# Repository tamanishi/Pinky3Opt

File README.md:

# Pinky3Opt

## Firmware

<https://github.com/tamanishi/qmk_firmware/tree/pinky3opt>

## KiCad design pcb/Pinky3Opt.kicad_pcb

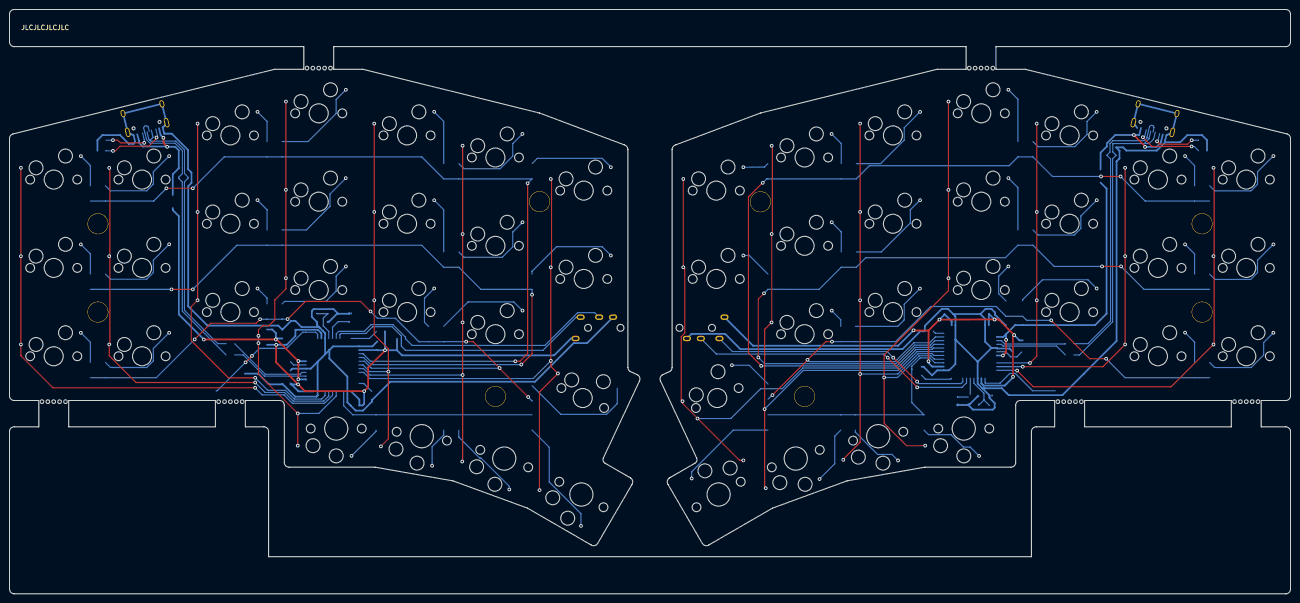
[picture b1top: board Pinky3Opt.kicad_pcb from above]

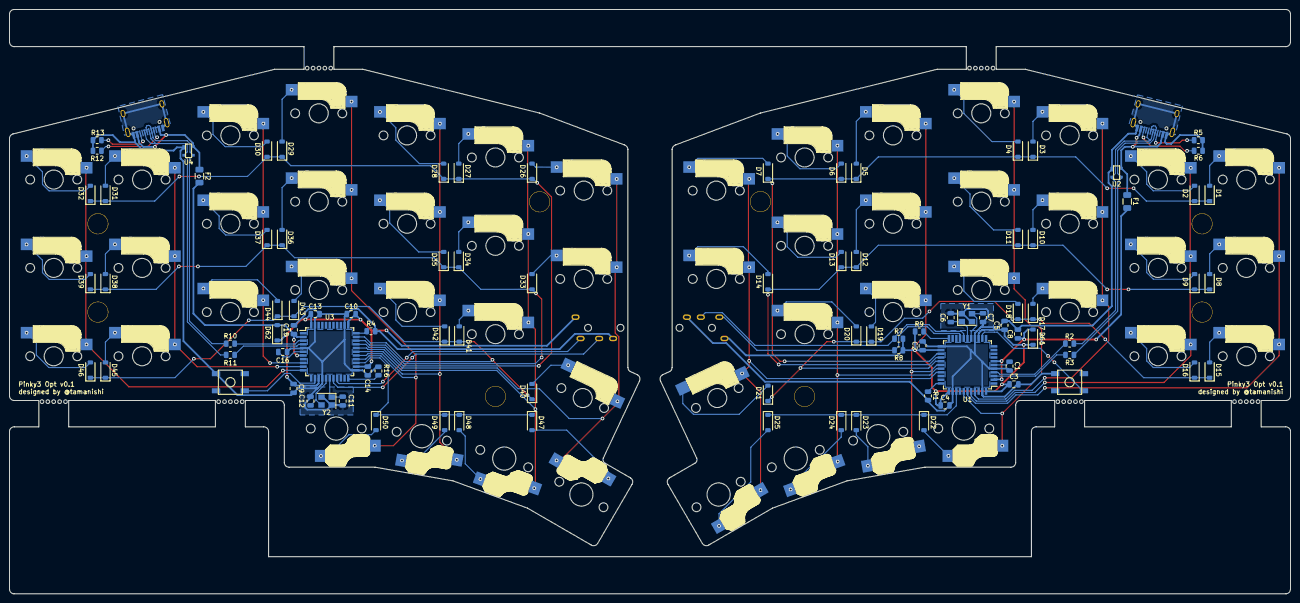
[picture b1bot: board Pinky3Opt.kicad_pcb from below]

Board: 2 copper layers, 276.2 x 126.0 mm, 154 parts (96 on the bottom side), 108 nets.

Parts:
C1, C16: 1uF; C_0805_2012Metric
C2, C3, C4, C5, C9, C10, C13, C14: 0.1uF; C_0805_2012Metric
C6, C7, C11, C12: 22pF; C_0805_2012Metric
C8, C15: 10uF; C_0805_2012Metric
D1, D2, D3, D4, D5, D6, D7, D8, D9, D10, D11, D12, D13, D14, D15, D16, D17, D18, D19, D20, D21, D22, D23, D24, D25, D26, D27, D28, D29, D30, D31, D32, D33, D34, D35, D36, D37, D38, D39, D40, D41, D42, D43, D44, D45, D46, D47, D48, D49, D50: D; D_SOD-123
D61, D62: D_Schottky; D_SOD-123
F1, F2: 500mA; Fuse_1206_3216Metric
J1, J3: USB_C_Receptacle_USB2.0; USB_C_Receptacle_HRO_TYPE-C-31-M-12
J2, J4: Conn_01x04; PJ-3200B-4A-Assembly
MX1, MX2, MX3, MX4, MX5, MX6, MX7, MX8, MX9, MX10, MX11, MX12, MX13, MX14, MX15, MX16, MX17, MX18, MX19, MX20, MX21, MX26, MX27, MX28, MX29, MX30, MX31, MX32, MX33, MX34, MX35, MX36, MX37, MX38, MX39, MX40, MX41, MX42, MX43, MX44, MX45, MX46: MX-NoLED; CherryMX_Hotswap
MX22, MX23, MX24, MX25, MX47, MX48, MX49, MX50: MX-NoLED; ChocV1_V2_Hotswap
R1, R4, R9, R16: 10kΩ; R_0805_2012Metric
R2, R3, R10, R11: 22Ω; R_0805_2012Metric
R5, R6, R12, R13: 5.1kΩ; R_0805_2012Metric
R7, R8: 4.7kΩ; R_0805_2012Metric
Ref**: Val**; m2_Spacer_Hole
Ref**#2, Ref**#3, Ref**#4, Ref**#5, Ref**#6, Ref**#7, Ref**#8: Val**; m2_Spacer_Hole
SW1, SW2: Reset; SKQGADE010
U1, U3: ATmega32U4-A; TQFP-44_10x10mm_P0.8mm
U2, U4: PRTR5V0U2X; SOT143B
Y1, Y2: 16MHz; Crystal_SMD_3225-4Pin_3.2x2.5mm

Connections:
+5V: C2.1, C3.1, C4.1, C5.1, D61.1 (K), J2.4, R7.1, R8.1, R9.2, U1.14 (VCC), U1.24 (AVCC), U1.34 (VCC), U1.44 (AVCC)
+5VA: C9.1, C10.1, C13.1, C14.1, D62.1 (K), J4.4, U3.14 (VCC), U3.24 (AVCC), U3.34 (VCC), U3.44 (AVCC)
/COL0_L: MX1.1 (COL), MX8.1 (COL), MX15.1 (COL), U1.39 (PF4)
/COL0_R: MX26.1 (COL), MX33.1 (COL), MX40.1 (COL), MX47.1 (COL), U3.29 (PB5)
/COL1_L: MX2.1 (COL), MX9.1 (COL), MX16.1 (COL), U1.40 (PF1)
/COL1_R: MX27.1 (COL), MX34.1 (COL), MX41.1 (COL), MX48.1 (COL), U3.28 (PB4)
/COL2_L: MX3.1 (COL), MX10.1 (COL), MX17.1 (COL), U1.41 (PF0)
/COL2_R: MX28.1 (COL), MX35.1 (COL), MX42.1 (COL), MX49.1 (COL), U3.27 (PD7)
/COL3_L: MX4.1 (COL), MX11.1 (COL), MX18.1 (COL), MX22.1 (COL), U1.38 (PF5)
/COL3_R: MX29.1 (COL), MX36.1 (COL), MX43.1 (COL), MX50.1 (COL), U3.26 (PD6)
/COL4_L: MX5.1 (COL), MX12.1 (COL), MX19.1 (COL), MX23.1 (COL), U1.28 (PB4)
/COL4_R: MX30.1 (COL), MX37.1 (COL), MX44.1 (COL), U3.9 (PB1)
/COL5_L: MX6.1 (COL), MX13.1 (COL), MX20.1 (COL), MX24.1 (COL), U1.29 (PB5)
/COL5_R: MX31.1 (COL), MX38.1 (COL), MX45.1 (COL), U3.10 (PB2)
/COL6_L: MX7.1 (COL), MX14.1 (COL), MX21.1 (COL), MX25.1 (COL), U1.30 (PB6)
/COL6_R: MX32.1 (COL), MX39.1 (COL), MX46.1 (COL), U3.11 (PB3)
/D+_L: R2.2, U1.4 (D+)
/D+_R: R11.2, U3.4 (D+)
/D-_L: R3.2, U1.3 (D-)
/D-_R: R10.2, U3.3 (D-)
/HDETECT_L: R9.1, U1.22 (PD5)
/HDETECT_R: R16.1, U3.22 (PD5)
/ROW0_L: D1.1 (K), D2.1 (K), D3.1 (K), D4.1 (K), D5.1 (K), D6.1 (K), D7.1 (K), U1.25 (PD4)
/ROW0_R: D26.1 (K), D27.1 (K), D28.1 (K), D29.1 (K), D30.1 (K), D31.1 (K), D32.1 (K), U3.30 (PB6)
/ROW1_L: D8.1 (K), D9.1 (K), D10.1 (K), D11.1 (K), D12.1 (K), D13.1 (K), D14.1 (K), U1.26 (PD6)
/ROW1_R: D33.1 (K), D34.1 (K), D35.1 (K), D36.1 (K), D37.1 (K), D38.1 (K), D39.1 (K), U3.31 (PC6)
/ROW2_L: D15.1 (K), D16.1 (K), D17.1 (K), D18.1 (K), D19.1 (K), D20.1 (K), D21.1 (K), U1.27 (PD7)
/ROW2_R: D40.1 (K), D41.1 (K), D42.1 (K), D43.1 (K), D44.1 (K), D45.1 (K), D46.1 (K), U3.32 (PC7)
/ROW3_L: D22.1 (K), D23.1 (K), D24.1 (K), D25.1 (K), U1.36 (PF7)
/ROW3_R: D47.1 (K), D48.1 (K), D49.1 (K), D50.1 (K), U3.25 (PD4)
/SCL_L: J2.2, R7.2, U1.18 (PD0)
/SCL_R: J4.2, U3.18 (PD0)
/SDA_L: J2.3, R8.2, U1.19 (PD1)
/SDA_R: J4.3, U3.19 (PD1)
GND: C1.2, C2.2, C3.2, C4.2, C5.2, C6.1, C7.1, C8.2, J1.A1 (GND), J1.A12 (GND), J1.B1 (GND), J1.B12 (GND), J1.S1 (SHIELD), J2.1, R1.2, R5.2, R6.2, SW1.1, U1.5 (UGND), U1.15 (GND), U1.23 (GND), U1.35 (GND), U1.43 (GND), U2.1 (GND), Y1.2, Y1.4
GNDA: C9.2, C10.2, C11.1, C12.1, C13.2, C14.2, C15.2, C16.2, J3.A1 (GND), J3.A12 (GND), J3.B1 (GND), J3.B12 (GND), J3.S1 (SHIELD), J4.1, R4.2, R12.2, R13.2, R16.2, SW2.1, U3.5 (UGND), U3.15 (GND), U3.23 (GND), U3.35 (GND), U3.43 (GND), U4.1 (GND), Y2.2, Y2.4
unnamed: D1.2 (A), MX1.2 (ROW)
unnamed: D2.2 (A), MX2.2 (ROW)
unnamed: D3.2 (A), MX3.2 (ROW)
unnamed: D4.2 (A), MX4.2 (ROW)
unnamed: D5.2 (A), MX5.2 (ROW)
unnamed: D6.2 (A), MX6.2 (ROW)
unnamed: D7.2 (A), MX7.2 (ROW)
unnamed: D8.2 (A), MX8.2 (ROW)
unnamed: D9.2 (A), MX9.2 (ROW)
unnamed: D10.2 (A), MX10.2 (ROW)
unnamed: D11.2 (A), MX11.2 (ROW)
unnamed: D12.2 (A), MX12.2 (ROW)
unnamed: D13.2 (A), MX13.2 (ROW)
unnamed: D14.2 (A), MX14.2 (ROW)
unnamed: D15.2 (A), MX15.2 (ROW)
unnamed: D16.2 (A), MX16.2 (ROW)
unnamed: D17.2 (A), MX17.2 (ROW)
unnamed: D18.2 (A), MX18.2 (ROW)
unnamed: D19.2 (A), MX19.2 (ROW)
unnamed: D20.2 (A), MX20.2 (ROW)
unnamed: D21.2 (A), MX21.2 (ROW)
unnamed: D22.2 (A), MX22.2 (ROW)
unnamed: D23.2 (A), MX23.2 (ROW)
unnamed: D24.2 (A), MX24.2 (ROW)
unnamed: D25.2 (A), MX25.2 (ROW)
unnamed: D26.2 (A), MX26.2 (ROW)
unnamed: D27.2 (A), MX27.2 (ROW)
unnamed: D28.2 (A), MX28.2 (ROW)
unnamed: D29.2 (A), MX29.2 (ROW)
unnamed: D30.2 (A), MX30.2 (ROW)
unnamed: D31.2 (A), MX31.2 (ROW)
unnamed: D32.2 (A), MX32.2 (ROW)
unnamed: D33.2 (A), MX33.2 (ROW)
unnamed: D34.2 (A), MX34.2 (ROW)
unnamed: D35.2 (A), MX35.2 (ROW)
unnamed: D36.2 (A), MX36.2 (ROW)
unnamed: D37.2 (A), MX37.2 (ROW)
unnamed: D38.2 (A), MX38.2 (ROW)
unnamed: D39.2 (A), MX39.2 (ROW)
unnamed: D40.2 (A), MX40.2 (ROW)
unnamed: D41.2 (A), MX41.2 (ROW)
unnamed: D42.2 (A), MX42.2 (ROW)
unnamed: D43.2 (A), MX43.2 (ROW)
unnamed: D44.2 (A), MX44.2 (ROW)
unnamed: D45.2 (A), MX45.2 (ROW)
unnamed: D46.2 (A), MX46.2 (ROW)
unnamed: D47.2 (A), MX47.2 (ROW)
unnamed: D48.2 (A), MX48.2 (ROW)
unnamed: D49.2 (A), MX49.2 (ROW)
unnamed: D50.2 (A), MX50.2 (ROW)
unnamed: J1.A5 (CC1), R5.1
unnamed: J1.B5 (CC2), R6.1
unnamed: J3.A5 (CC1), R12.1
unnamed: J3.B5 (CC2), R13.1
unnamed: C1.1, U1.6 (UCAP)
unnamed: C6.2, U1.17 (XTAL1), Y1.1
unnamed: C7.2, U1.16 (XTAL2), Y1.3
unnamed: R1.1, U1.33 (~HWB/PE2)
unnamed: SW1.2, U1.13 (~RESET)
unnamed: J1.A6 (D+), J1.B6 (D+), R2.1, U2.2 (IO1)
unnamed: J1.A7 (D-), J1.B7 (D-), R3.1, U2.3 (IO2)
unnamed: C16.1, U3.6 (UCAP)
unnamed: C11.2, U3.17 (XTAL1), Y2.1
unnamed: C12.2, U3.16 (XTAL2), Y2.3
unnamed: R4.1, U3.33 (~HWB/PE2)
unnamed: SW2.2, U3.13 (~RESET)
unnamed: J3.A6 (D+), J3.B6 (D+), R11.1, U4.2 (IO1)
unnamed: J3.A7 (D-), J3.B7 (D-), R10.1, U4.3 (IO2)
VBUS: C8.1, D61.2 (A), F1.2, U1.2 (UVCC), U1.7 (VBUS)
VCC: F1.1, J1.A4 (VBUS), J1.A9 (VBUS), J1.B4 (VBUS), J1.B9 (VBUS), U2.4 (VCC)
VDC: C15.1, D62.2 (A), F2.2, U3.2 (UVCC), U3.7 (VBUS)
VDD: F2.1, J3.A4 (VBUS), J3.A9 (VBUS), J3.B4 (VBUS), J3.B9 (VBUS), U4.4 (VCC)

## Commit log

2023-03-11 add schematic/footprint libraries
2023-03-11 mcu and usb-c connector
2023-03-11 add usb-c connector library
2023-03-11 add schematic/footprint library
2023-03-11 left hand schematic
2023-03-11 fix erc error
2023-03-15 rows and cols to mcu
2023-03-15 through hole
2023-03-15 socket pad via
2023-03-18 maybe done left hand
2023-03-18 tweak
2023-03-21 maybe done right hand
2023-03-21 breakaway
2023-03-21 silkscreen
2023-03-25 jlcpcb pcba configuration
2023-03-25 top plate
2023-03-25 bottom plate
2023-03-25 remove parts from top plate
2023-03-25 pcb editor page size
2023-03-25 silk
2023-03-26 trrs bottom side
2023-07-01 readme
2023-07-01 Create LICENSE
2023-07-01 add images
2023-07-03 firmware
